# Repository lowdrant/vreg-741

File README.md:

# vreg-741
Variable linear voltage regulator based on the classic 741 op amp

## License
If you use this PCB, specifically the files used with PCBNew, in a design or as the basis for a design, excepting as an educational reference or example, I request that you leave my name on the circuit board and credit me accordingly for the design. Excepting any attempt to copyright this design, I place no further requirements or restrictions on its use, replication, fabrication, or any other purpose. 

The schematic itself is of a basic voltage regulation circuit, which I believe cannot be rightfully claimed as intellectual property.

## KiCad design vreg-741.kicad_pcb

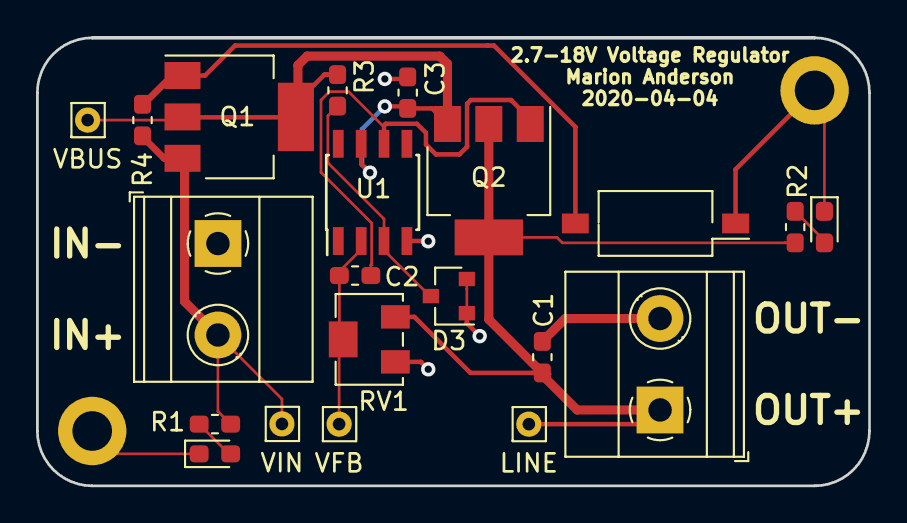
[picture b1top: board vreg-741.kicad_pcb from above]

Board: 2 copper layers, 46.2 x 24.9 mm, 23 parts (0 on the bottom side), 10 nets.

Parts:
C1, C2: 100p; C_0603_1608Metric_Pad1.05x0.95mm_HandSolder
C3: 100n; C_0603_1608Metric_Pad1.05x0.95mm_HandSolder
D1, D2: 475-2486-1-ND; LED_0603_1608Metric_Pad1.05x0.95mm_HandSolder
D3: MMBZ5223BLT1G; D_SOT-23_ANK
H2, H3: MountingHole_Pad; MountingHole_2.2mm_M2_DIN965_Pad
J1, J2: 1729128; TerminalBlock_Phoenix_MKDS-1,5-2-5.08_1x02_P5.08mm_Horizont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
LINE: TestPoint; Pin_D0.7mm_L6.5mm_W1.8mm_FlatFork
Q1: FQT5P10; SOT-223-3_TabPin2
Q2: 2STN1550; SOT-223-3_TabPin2
R1, R2, R4: 10k; R_0603_1608Metric_Pad1.05x0.95mm_HandSolder
R3: 1k; R_0603_1608Metric_Pad1.05x0.95mm_HandSolder
RV1: 3214W-1-105E; Potentiometer_Bourns_3214W_Vertical
SW1: A6SN-1104; SW_DIP_SPSTx01_Slide_Omron_A6S-110x_W8.9mm_P2.54mm
U1: UA741CDR‎; SOIC-8_3.9x4.9mm_P1.27mm
VBUS: TestPoint; Pin_D0.7mm_L6.5mm_W1.8mm_FlatFork
VFB: TestPoint; Pin_D0.7mm_L6.5mm_W1.8mm_FlatFork
VIN: TestPoint; Pin_D0.7mm_L6.5mm_W1.8mm_FlatFork

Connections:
/VFB: C2.2, RV1.2, U1.2, VFB.1
/VIN: J1.2, Q1.3, R1.1, R4.1, VIN.1
/VZ: D3.1, R3.2, U1.3
GND: C1.2, C3.2, D1.1, D2.1, D3.2, H2.1, H3.1, J1.1, J2.2, RV1.1, SW1.1, U1.4
LINE: C1.1, J2.1, LINE.1, Q2.2, R2.1, RV1.3
unnamed: C2.1, Q2.1, U1.6
unnamed: D1.2, R1.2
unnamed: D2.2, R2.2
unnamed: Q1.1, R4.2, SW1.2
VBUS: C3.1, Q1.2, Q2.3, R3.1, U1.7, VBUS.1

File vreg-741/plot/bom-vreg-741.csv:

"Id";"Designator";"Package";"Quantity";"Designation";"Supplier and ref";
1;"SW1";"SW_DIP_SPSTx01_Slide_Omron_A6S-110x_W8.9mm_P2.54mm";1;"A6SX-1104";;;
2;"J2,J1";"TerminalBlock_Phoenix_MKDS-1,5-2-5.08_1x02_P5.08mm_Horizontal";2;"Screw_Terminal_01x02";;;
3;"VFB,VIN,VBUS,LINE";"Pin_D0.7mm_L6.5mm_W1.8mm_FlatFork";4;"TestPoint";;;
4;"D1,D2";"LED_0603_1608Metric_Pad1.05x0.95mm_HandSolder";2;"LED";;;
5;"H2,H3";"MountingHole_2.2mm_M2_DIN965_Pad";2;"MountingHole_Pad";;;
6;"U1";"SOIC-8_3.9x4.9mm_P1.27mm";1;"UA741";;;
7;"Q2";"SOT-223-3_TabPin2";1;"2STN1550";;;
8;"G***";"caribiner-bsilks";1;"caribiner-bsilks";;;
9;"D3";"D_SOT-23_ANK";1;"MMBZ5223BLT1G";;;
10;"C1,C2";"C_0603_1608Metric_Pad1.05x0.95mm_HandSolder";2;"100p";;;
11;"C3";"C_0603_1608Metric_Pad1.05x0.95mm_HandSolder";1;"100n";;;
12;"R1,R2,R4";"R_0603_1608Metric_Pad1.05x0.95mm_HandSolder";3;"10k";;;
13;"R3";"R_0603_1608Metric_Pad1.05x0.95mm_HandSolder";1;"1k";;;
14;"Q1";"SOT-223-3_TabPin2";1;"FQT5P10";;;
15;"RV1";"Potentiometer_Bourns_3214W_Vertical";1;"3214W-1-105E";;;

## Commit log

2020-04-05 updated part numbers and added manufacturer field
2020-04-06 extra easter eggs
2020-06-23 Update README.md with license
2020-06-23 Updated license to be more specific
